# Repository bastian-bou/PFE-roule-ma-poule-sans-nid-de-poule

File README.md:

# PFE Roule ma poule

Pour avoir des informations, allez dans **docs**, pour le code source c'est **dev** et pour les schémas et la carte finale c'est **Hardware**

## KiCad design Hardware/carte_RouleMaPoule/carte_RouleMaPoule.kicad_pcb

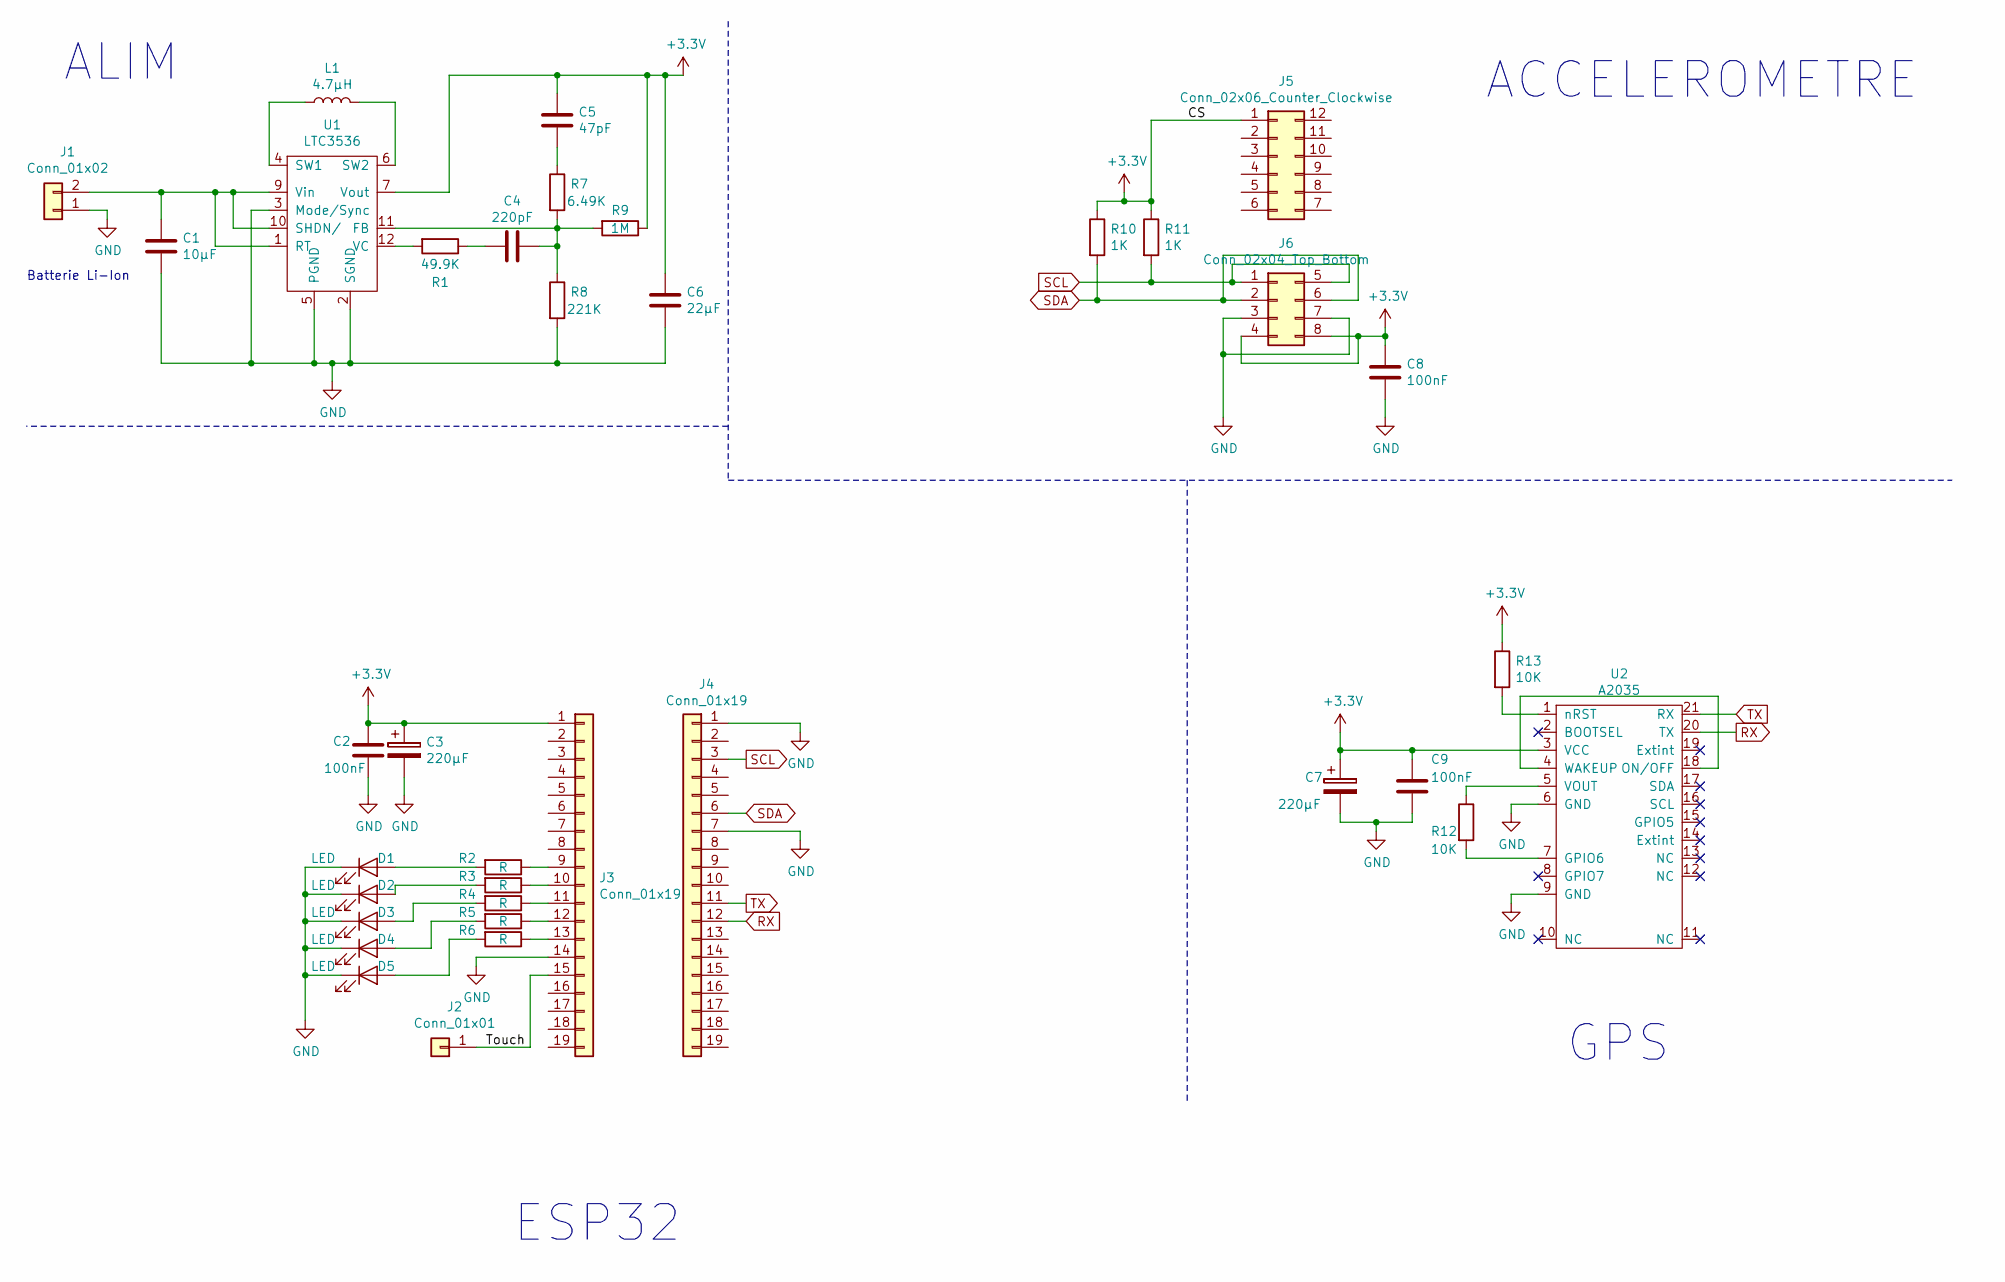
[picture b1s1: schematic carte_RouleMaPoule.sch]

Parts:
C1: 10µF; C_1206_3216Metric
C2, C8, C9: 100nF; C_1206_3216Metric
C3, C7: 220µF; CP_Elec_6.3x7.7
C4: 220pF; C_1206_3216Metric
C5: 47pF; C_1206_3216Metric
C6: 22µF; C_1206_3216Metric
D1, D2, D3, D4, D5: LED; LED_1210_3225Metric
J1: Conn_01x02; JST_PH_B2B-PH-K_1x02_P2.00mm_Vertical
J2: Conn_01x01; Pin_D0.7mm_L6.5mm_W1.8mm_FlatFork
J3, J4: Conn_01x19; PinHeader_1x19_P2.54mm_Vertical
J5: Conn_02x06_Counter_Clockwise; PinHeader_2x06_P2.54mm_Vertical
J6: Conn_02x04_Top_Bottom; PinHeader_2x04_P2.54mm_Vertical
L1: 4.7µH; L_1210_3225Metric; Farnell 2871486
R1: 49.9K; R_1206_3216Metric
R2, R3, R4, R5, R6: R; R_1206_3216Metric
R7: 6.49K; R_1206_3216Metric
R8: 221K; R_1206_3216Metric
R9: 1M; R_1206_3216Metric
R10, R11: 1K; R_1206_3216Metric
R12, R13: 10K; R_1206_3216Metric
U1: LTC3536; MSOP-12-1EP_3x4mm_P0.65mm_EP1.65x2.85mm
U2: A2035

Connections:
+3V3: C2.1, C3.1, C5.1, C6.1, C7.1, C8.1, C9.1, J3.1, J5.1, J6.4, J6.8, R9.1, R10.1, R11.1, R13.1, U1.7 (Vout), U2.3 (VCC)
/Touch: J2.1, J3.15
GND: C1.2, C2.2, C3.2, C6.2, C7.2, C8.2, C9.2, D1.1 (K), D2.1 (K), D3.1 (K), D4.1 (K), D5.1 (K), J1.1, J3.14, J4.1, J4.7, J6.3, J6.7, R8.2, U1.2 (SGND), U1.3 (Mode/Sync), U1.5 (PGND), U1.13 (PGND), U2.6 (GND), U2.9 (GND)
unnamed: C1.1, J1.2, U1.1 (RT), U1.8 (Vin), U1.9 (Vin), U1.10 (SHDN/)
unnamed: C4.1, R7.2, R8.1, R9.2, U1.11 (FB)
unnamed: C4.2, R1.1
unnamed: C5.2, R7.1
unnamed: D1.2 (A), R2.2
unnamed: D2.2 (A), R3.2
unnamed: D3.2 (A), R4.2
unnamed: D4.2 (A), R5.2
unnamed: D5.2 (A), R6.2
unnamed: J3.9, R2.1
unnamed: J3.10, R3.1
unnamed: J3.11, R4.1
unnamed: J3.12, R5.1
unnamed: J3.13, R6.1
unnamed: L1.1, U1.4 (SW1)
unnamed: L1.2, U1.6 (SW2)
unnamed: R1.2, U1.12 (VC)
unnamed: R12.1, U2.5 (VOUT)
unnamed: R12.2, U2.7 (GPIO6)
unnamed: R13.2, U2.1 (nRST)
unnamed: U2.4 (WAKEUP), U2.18 (ON/OFF)
RX: J4.12, U2.20 (TX)
SCL: J4.3, J6.1, J6.5, R11.2
SDA: J4.6, J6.2, J6.6, R10.2
TX: J4.11, U2.21 (RX)

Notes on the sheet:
ESP32
GPS
ACCELEROMETRE
ALIM
Batterie Li-Ion

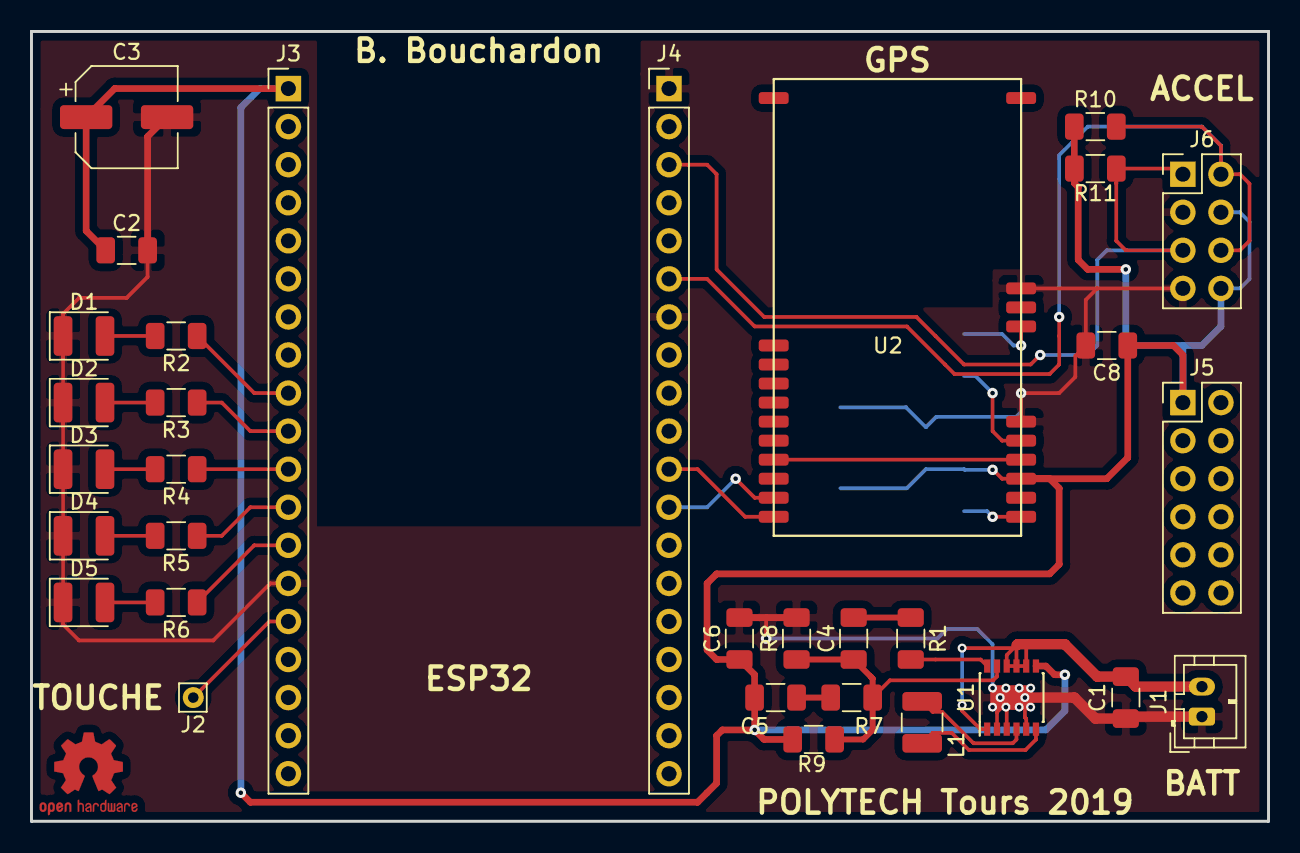
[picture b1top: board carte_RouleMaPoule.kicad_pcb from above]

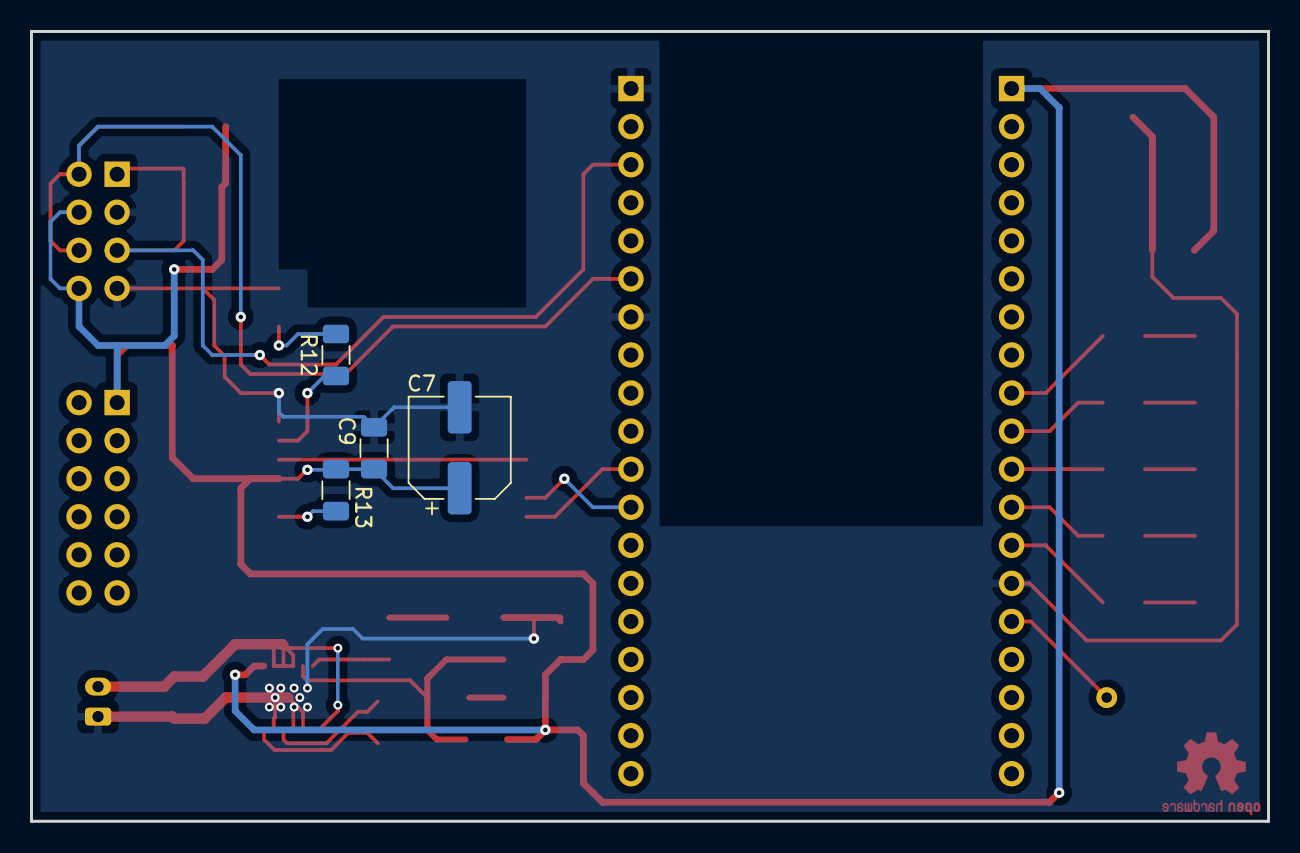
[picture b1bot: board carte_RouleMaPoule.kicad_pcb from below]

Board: 2 copper layers, 82.5 x 52.7 mm, 36 parts (4 on the bottom side), 28 nets.

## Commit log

2019-06-24 add all the project in github
